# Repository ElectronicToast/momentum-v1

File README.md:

# momentum-v1
An elegant circuit board for a more civilized age

<p align="center">
  <b>Star Wars: Revenge of the Ditch<br>
     26 May 2023</b><br>
</p>

## Description
This is a simple prop controller designed for a Ditch Day stack at Caltech. [Ditch Day](https://www.pasadenanow.com/main/ditch-day-on-friday-caltech-seniors-create-a-whirlwind-of-fun-and-challenges) is a tradition where undergraduate seniors design elaborate themed experiences, called "stacks", for the enjoyment of younger students on a date kept secret until the last minute.

This Ditch Day stack featured custom lightsabers with WS2812 LED lighting and motion-reactive sound effects. This repository contains the hardware and firmware used in the lightsabers.

## Hardware
- Raspberry Pi Pico
- MT-3608 boost converter module, permitting flexible power input (designed for 2S D cell batteries)
- 1x WS2812 LED output with 5V buffer
- PAM8302 2.5W Class-D audio amplifier
- 2x pushbutton input with RC debouncing 
- Socket for MPU-6050 IMU

Fabrication output is generated using [KiKit](https://github.com/yaqwsx/KiKit), targeting the JLCPCB assembly service. It is recommended to order panels to lower costs; 10 panels of 4 were fabricated for Ditch Day with a target of 20 production units.

- [Schematic](https://github.com/ElectronicToast/momentum-v1/blob/main/board/doc/momentum.pdf)
- [Interactive BOM](http://htmlpreview.github.io/?https://github.com/ElectronicToast/momentum-v1/blob/main/board/doc/ibom.html)

## Firmware
The code is written using the Raspberry Pi Pico C SDK and has been tested to build and run properly on Ubuntu 22.04 LTS (with the Pico SDK installed per Raspberry Pi's instructions) and Windows (using the [Windows installer](https://github.com/raspberrypi/pico-setup-windows)).  

## Assembly Notes
- The MPU-6050 is intended to fit over the MT-3608 boost converter. Header pins can be soldered to the MPU-6050, then soldered into the row of pins on the PCB. Take care to respect the orientation.
- The LED output pads are not in the same order as a typical WS2812 strip (board errata).
- There is no reverse polarity protection, though the MT-3608 may be tolerant of reverse polarity.

## Usage
`uf2` binaries as used for Ditch Day are provided in `firmware/bin/`. The nomenclature `44k1r2` refers to audio at 44.1 kHz sampling rate and with every sample repeated twice (so PWM clock frequency of 44.1 kHz * 2 * 256).

To modify the code,
1. Install the Pico C SDK, including `pico-extras`. You might also install Visual Studio Code and the relevant extensions (CMake, C/C++, etc.) if you prefer an IDE.
2. Modify definitions in `config.h` as appropriate for e.g. flash-on-clash animations
3. From `firmware/src/`, `mkdir build`
4. `cd build`
5. `cmake ..`
6. `make` (or `ninja` if using the Windows SDK installer)

Upload the code as with any RP2040 binary using the USB bootloader (plug in USB while holding down BOOTSEL on the Pico, and drag-and-drop the `.uf2` file into the `RPI-P2` 'flash drive' that appears.

## Customizing sounds
A converter utility Python script is provided, which takes a set of WAV files (one `poweron.wav` 'ignition' sound, one `poweroff.wav` deactivation sound, one 'hum.wav' idle sound, and any number of `clash0.wav` `clash1.wav`... clash sounds and `swing0.wav` `swing1.wav`... swing sounds) and creates a C header file with `uint8_t` arrays and suitable definitions. 

If you would like to use your own sounds, convert them to WAV, run the Python script on them, and include the generated `.h` file in `speaker.c`.

## Future Improvements
- Single custom PCB with more flash (RP2040 supports up to 16 MB versus Pico stock 2 MB)
- SD card support
- Motion detection uses interrupt features of MPU-6050, which use only the accelerometer. Clash and swing sensing can be improved.
- Due to budget, there is no physical power switch, and WS2812s have high quiescent current. Add a physical power switch or a MOSFET.
- Design for Li-Ion power versus 2S D-cell (chosen for safety)

<p align="center">
  <b>Go to bed frosh, Ditch Day is Tomorrow!<br>
</p>

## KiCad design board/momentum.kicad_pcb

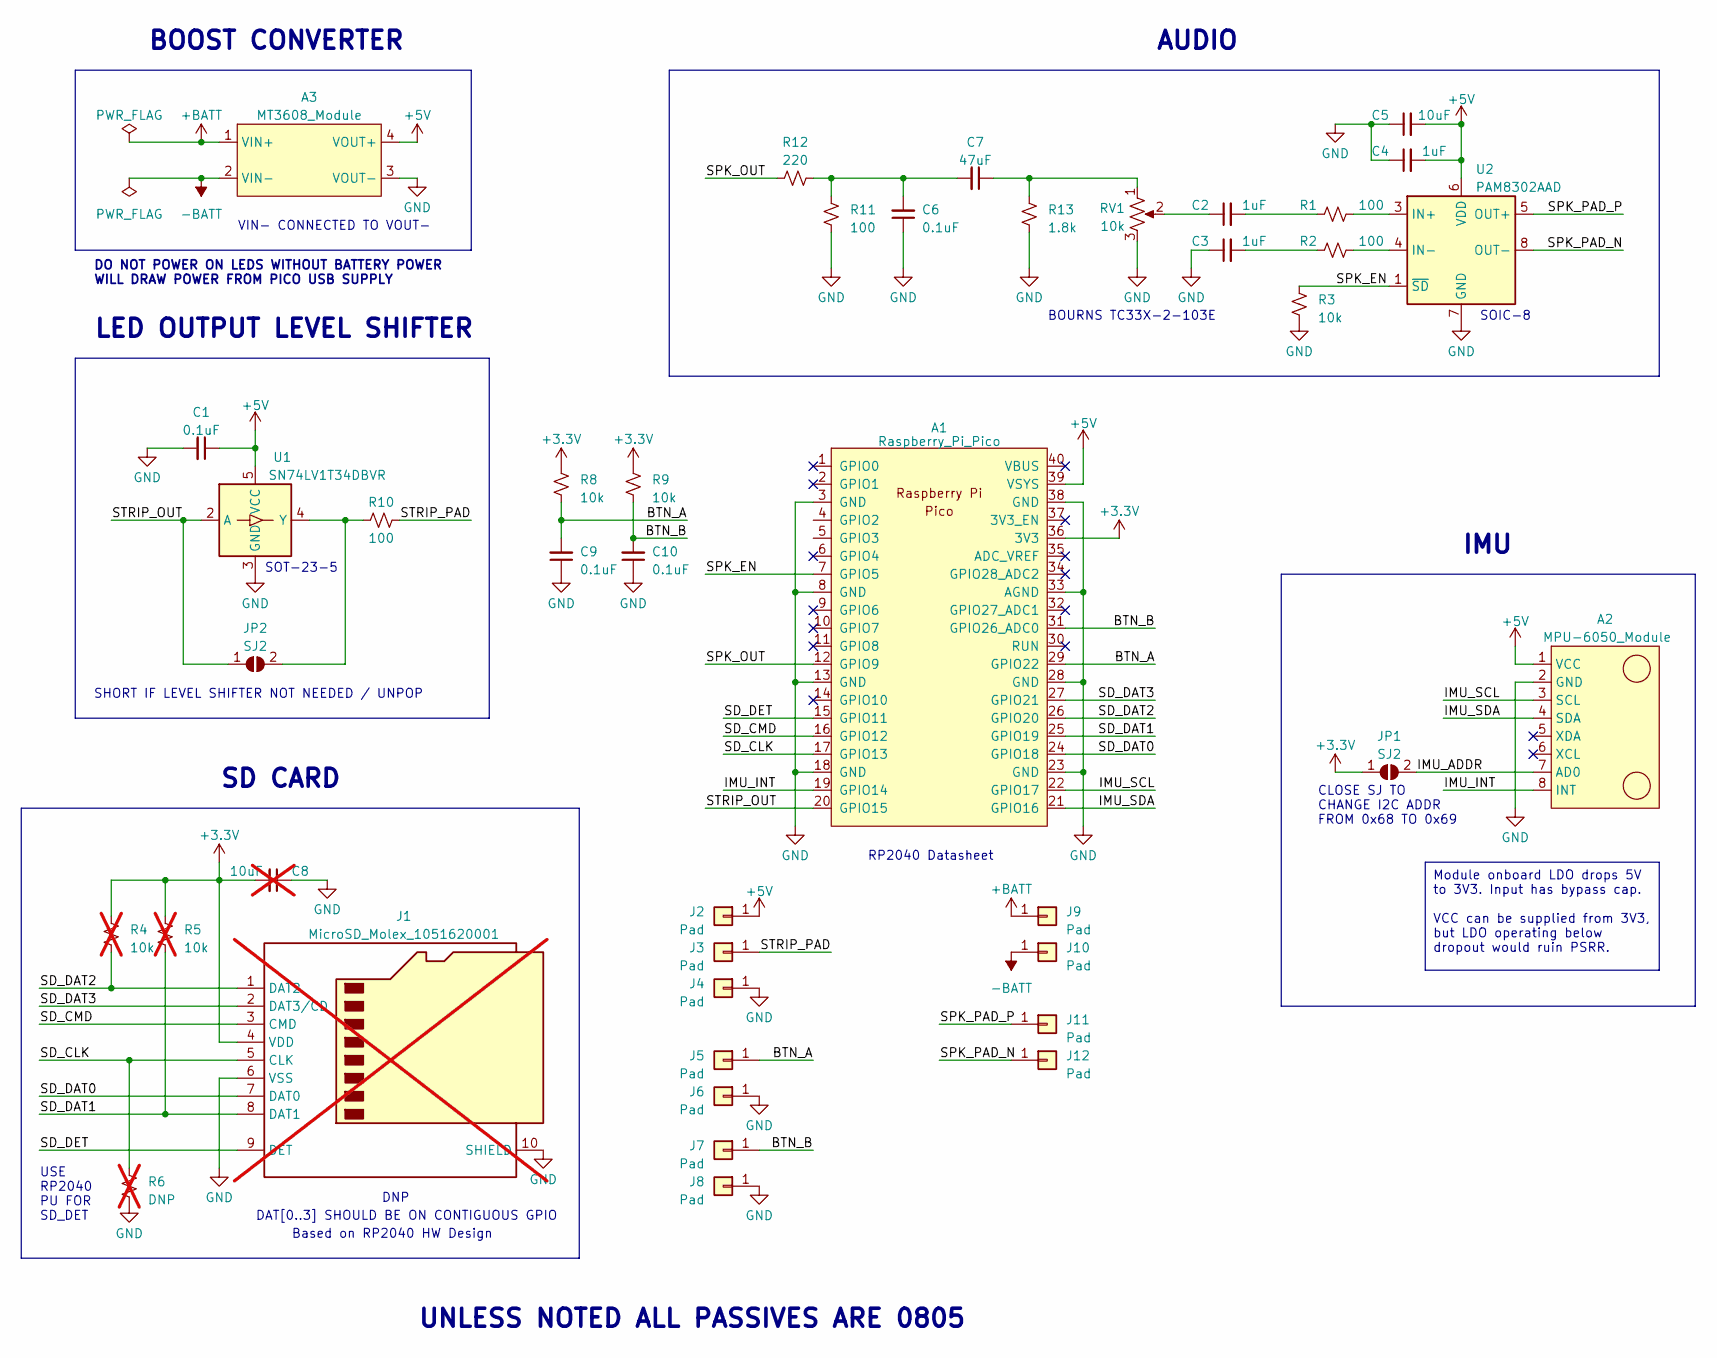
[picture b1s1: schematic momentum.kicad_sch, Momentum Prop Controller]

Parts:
A1: Raspberry_Pi_Pico; RPi_Pico_SMD_NoSWD_NoLabel; LCSC NA
A2: MPU-6050_Module; LCSC NA
A3: MT3608_Module; MT3608_Module_SMD; LCSC NA
C1, C6, C9, C10: 0.1uF; C_0805_2012Metric_Pad1.18x1.45mm_HandSolder; LCSC C28233
C2, C3, C4: 1uF; C_0805_2012Metric_Pad1.18x1.45mm_HandSolder; LCSC C28323
C5: 10uF; C_0805_2012Metric_Pad1.18x1.45mm_HandSolder; LCSC C15850
C7: 47uF; C_0805_2012Metric_Pad1.18x1.45mm_HandSolder; LCSC C16780
C8: 10uF; C_0805_2012Metric_Pad1.18x1.45mm_HandSolder_NoPaste; LCSC C15850; not fitted
J1: MicroSD_Molex_1051620001; MicroSD_Molex_1051620001_HandSoldering; LCSC NA; not fitted
J2, J3, J4, J5, J6, J7, J8, J9, J10, J11, J12: Pad; LCSC NA
JP1, JP2: SJ2; SolderJumper-2_P1.3mm_Open_Pad1.0x1.5mm; LCSC NA
R1, R2, R10, R11: 100; R_0805_2012Metric_Pad1.20x1.40mm_HandSolder; LCSC C17408
R3, R8, R9: 10k; R_0805_2012Metric_Pad1.20x1.40mm_HandSolder; LCSC C17414
R4, R5: 10k; R_0805_2012Metric_Pad1.20x1.40mm_HandSolder_NoPaste; JLCPCB_IGNORE Y; not fitted
R6: DNP; R_0805_2012Metric_Pad1.20x1.40mm_HandSolder_NoPaste; LCSC NA; not fitted
R12: 220; R_0805_2012Metric_Pad1.20x1.40mm_HandSolder; LCSC C17557
R13: 1.8k; R_0805_2012Metric_Pad1.20x1.40mm_HandSolder; LCSC C17398
RV1: 10k; Potentiometer_Bourns_TC33X_Vertical; LCSC C719176
U1: SN74LV1T34DBVR; SOT-23-5_HandSoldering; LCSC C100024
U2: PAM8302AAD; SOIC-8_3.9x4.9mm_P1.27mm; LCSC C112137

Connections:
+3.3V: A1.36 (3V3), C8.2, J1.4 (VDD), JP1.1 (A), R4.2, R5.2, R8.2, R9.2
+5V: A1.39 (VSYS), A2.1 (VCC), A3.4 (VOUT+), C1.1, C4.2, C5.2, J2.1, U1.5 (VCC), U2.6 (VDD)
+BATT: A3.1 (VIN+), J9.1
-BATT: A3.2 (VIN-), J10.1
/BTN_A: A1.29 (GPIO22), C9.2, J5.1, R8.1
/BTN_B: A1.31 (GPIO26_ADC0), C10.2, J7.1, R9.1
/IMU_ADDR: A2.7 (AD0), JP1.2 (B)
/IMU_INT: A1.19 (GPIO14), A2.8 (INT)
/IMU_SCL: A1.22 (GPIO17), A2.3 (SCL)
/IMU_SDA: A1.21 (GPIO16), A2.4 (SDA)
/SD_CLK: A1.17 (GPIO13), J1.5 (CLK), R6.2
/SD_CMD: A1.16 (GPIO12), J1.3 (CMD)
/SD_DAT0: A1.24 (GPIO18), J1.7 (DAT0)
/SD_DAT1: A1.25 (GPIO19), J1.8 (DAT1), R5.1
/SD_DAT2: A1.26 (GPIO20), J1.1 (DAT2), R4.1
/SD_DAT3: A1.27 (GPIO21), J1.2 (DAT3/CD)
/SD_DET: A1.15 (GPIO11), J1.9 (DET)
/SPK_EN: A1.7 (GPIO5), R3.2, U2.1 (~SD)
/SPK_OUT: A1.12 (GPIO9), R12.1
/SPK_PAD_N: J12.1, U2.8 (OUT-)
/SPK_PAD_P: J11.1, U2.5 (OUT+)
/STRIP_OUT: A1.20 (GPIO15), JP2.1 (A), U1.2 (A)
/STRIP_PAD: J3.1, R10.2
GND: A1.3 (GND), A1.8 (GND), A1.13 (GND), A1.18 (GND), A1.23 (GND), A1.28 (GND), A1.33 (AGND), A1.38 (GND), A2.2 (GND), A3.3 (VOUT-), C1.2, C3.1, C4.1, C5.1, C6.1, C8.1, C9.1, C10.1, J1.6 (VSS), J1.10 (SHIELD), J4.1, J6.1, J8.1, R3.1, R6.1, R11.2, R13.2, RV1.3, U1.3 (GND), U2.7 (GND)
unnamed: C2.1, RV1.2
unnamed: C2.2, R1.1
unnamed: C3.2, R2.1
unnamed: C6.2, C7.2, R11.1, R12.2
unnamed: C7.1, R13.1, RV1.1
unnamed: JP2.2 (B), R10.1, U1.4 (Y)
unnamed: R1.2, U2.3 (IN+)
unnamed: R2.2, U2.4 (IN-)

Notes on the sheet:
Module onboard LDO drops 5V to 3V3. Input has bypass cap. VCC can be supplied from 3V3, but LDO operating below dropout would ruin PSRR.
AUDIO
SOIC-8
DO NOT POWER ON LEDS WITHOUT BATTERY POWER WILL DRAW POWER FROM PICO USB SUPPLY
LED OUTPUT LEVEL SHIFTER
BOURNS TC33X-2-103E
SHORT IF LEVEL SHIFTER NOT NEEDED / UNPOP
VIN- CONNECTED TO VOUT-
Based on RP2040 HW Design
USE RP2040 PU FOR SD_DET
IMU
UNLESS NOTED ALL PASSIVES ARE 0805
DAT[0..3] SHOULD BE ON CONTIGUOUS GPIO
CLOSE SJ TO CHANGE I2C ADDR FROM 0x68 TO 0x69
RP2040 Datasheet
BOOST CONVERTER
SOT-23-5
DNP
SD CARD

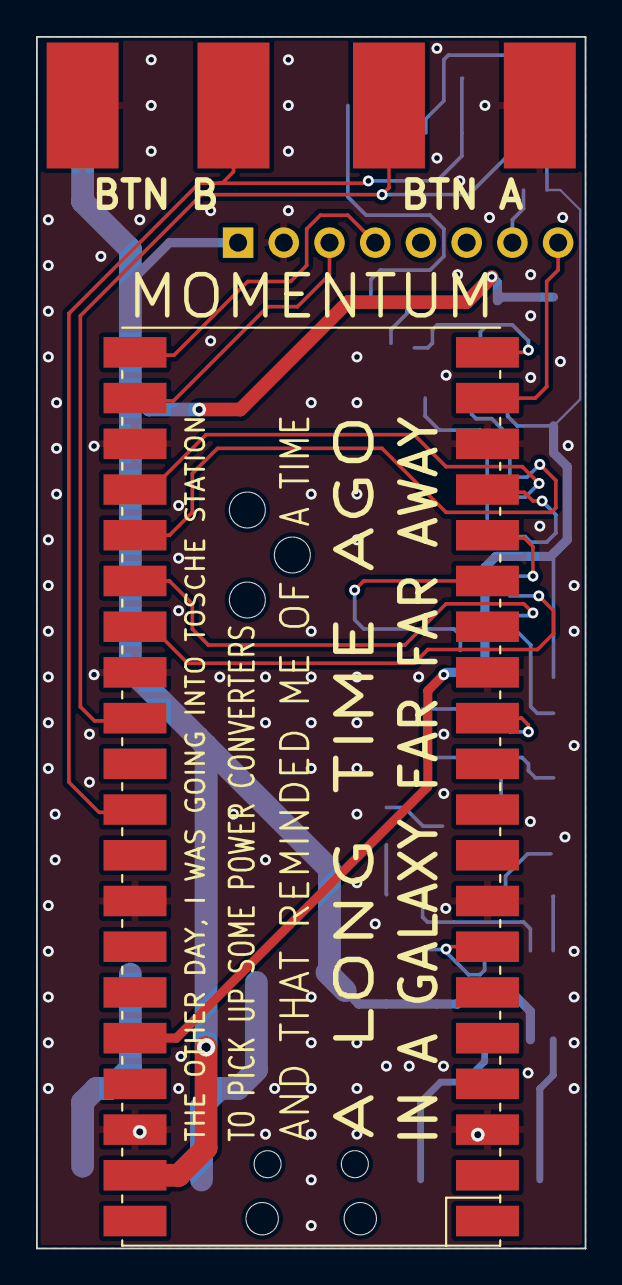
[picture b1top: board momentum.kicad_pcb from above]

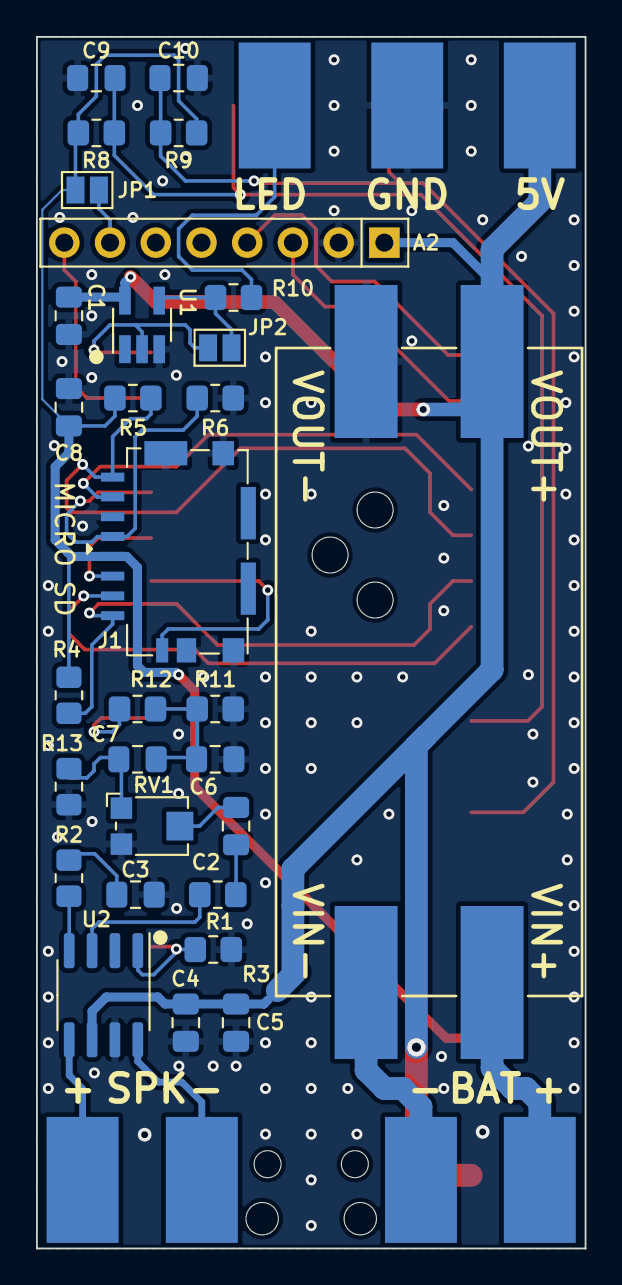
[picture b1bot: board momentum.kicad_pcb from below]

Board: 2 copper layers, 30.5 x 67.3 mm, 42 parts (37 on the bottom side), 32 nets.

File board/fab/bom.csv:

Comment,Designator,Footprint,LCSC
10k,"R3,R8,R9",Resistor_SMD:R_0805_2012Metric_Pad1.20x1.40mm_HandSolder,C17414
47uF,C7,Capacitor_SMD:C_0805_2012Metric_Pad1.18x1.45mm_HandSolder,C16780
100,"R1,R2,R10,R11",Resistor_SMD:R_0805_2012Metric_Pad1.20x1.40mm_HandSolder,C17408
0.1uF,"C1,C6,C9,C10",Capacitor_SMD:C_0805_2012Metric_Pad1.18x1.45mm_HandSolder,C28233
220,R12,Resistor_SMD:R_0805_2012Metric_Pad1.20x1.40mm_HandSolder,C17557
1uF,"C2,C3,C4",Capacitor_SMD:C_0805_2012Metric_Pad1.18x1.45mm_HandSolder,C28323
PAM8302AAD,U2,Package_SO:SOIC-8_3.9x4.9mm_P1.27mm,C112137
SN74LV1T34DBVR,U1,Package_TO_SOT_SMD:SOT-23-5_HandSoldering,C100024
1.8k,R13,Resistor_SMD:R_0805_2012Metric_Pad1.20x1.40mm_HandSolder,C17398
10k,RV1,Potentiometer_SMD:Potentiometer_Bourns_TC33X_Vertical,C719176
10uF,C5,Capacitor_SMD:C_0805_2012Metric_Pad1.18x1.45mm_HandSolder,C15850

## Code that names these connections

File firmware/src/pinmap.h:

/**
 * @file pinmap.h
 * @brief Raspberry Pi Pico pinout
 */


#ifndef _PINMAP_H_
#define _PINMAP_H_


// WS2812B LED strip
#define PIN_LEDSTRIP            15

// PAM8302 audio amplifier PWM output
#define PIN_SPK_PWM             9

// PAM8302 active high enable
#define PIN_SPK_EN              5     

// Pushbutton (Button A on board)
#define PIN_BTN                 22

// IMU
#define PIN_IMU_SDA             16
#define PIN_IMU_SCL             17
#define PIN_IMU_INT             14


#endif /* _PINMAP_H_ */

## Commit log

2023-05-29 Add files
